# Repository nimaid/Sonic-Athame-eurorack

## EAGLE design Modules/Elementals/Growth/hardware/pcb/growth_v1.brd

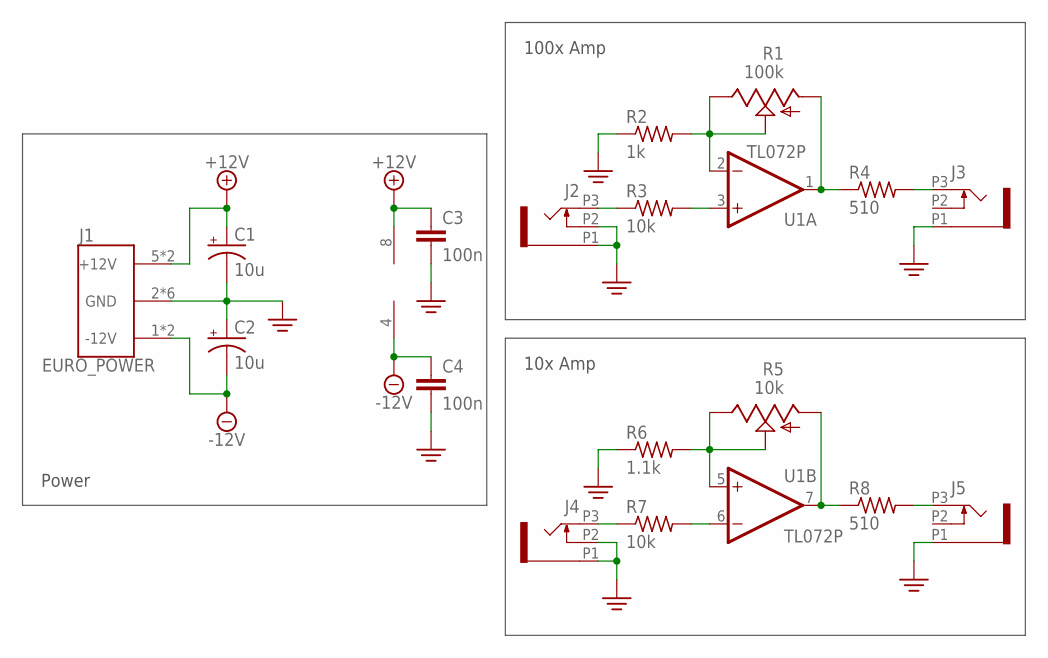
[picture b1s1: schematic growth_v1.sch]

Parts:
C1, C2: 10u; TT2D5L_FLIP
C3, C4: 100n; C025-024X044
J1: EURO_POWER
J2, J3, J4, J5: WQP-PJ398SM6; WQP_PJ_301M6
R1: 100k; ALPHA_POT_VERTICAL
R2: 1k; 0207/2V
R3, R7: 10k; 0207/2V
R4, R8: 510; 0207/2V
R5: 10k; ALPHA_POT_VERTICAL
R6: 1.1k; 0207/2V
U1: TL072P; DIL08

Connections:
+12V: C1.+, C3.1, J1.5 (+12V), J1.6 (+12V), U1.8 (V+)
-12V: C2.-, C4.1, J1.1 (-12V), J1.10 (-12V), U1.4 (V-)
GND: C1.-, C2.+, C3.2, C4.2, J1.2 (GND), J1.3 (GND), J1.4 (GND), J1.7 (GND), J1.8 (GND), J1.9 (GND), J2.P1 (1), J2.P2 (2), J3.P1 (1), J4.P1 (1), J4.P2 (2), J5.P1 (1), R2.1, R6.1
unnamed: R1.P$1 (E), R1.P$2 (S), R2.2, U1.2 (-IN)
unnamed: R1.P$3 (A), R4.1, U1.1 (OUT)
unnamed: R3.2, U1.3 (+IN)
unnamed: J2.P3 (3), R3.1
unnamed: J5.P3 (3), R8.2
unnamed: J3.P3 (3), R4.2
unnamed: R5.P$3 (A), R8.1, U1.7 (OUT)
unnamed: R5.P$1 (E), R5.P$2 (S), R6.2, U1.5 (+IN)
unnamed: R7.2, U1.6 (-IN)
unnamed: J4.P3 (3), R7.1

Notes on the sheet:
Power
100x Amp
10x Amp

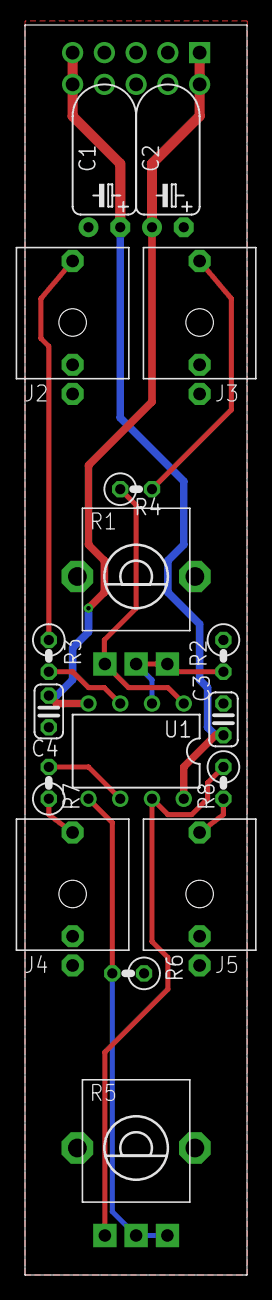
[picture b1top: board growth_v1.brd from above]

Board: 2 copper layers, 17.8 x 100.0 mm, 18 parts (1 on the bottom side), 13 nets.

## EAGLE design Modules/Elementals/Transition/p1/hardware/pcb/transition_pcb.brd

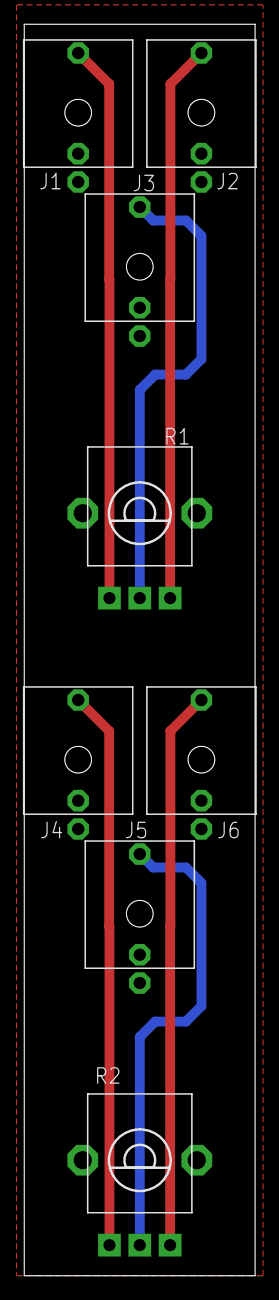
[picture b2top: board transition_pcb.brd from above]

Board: 2 copper layers, 19.0 x 103.2 mm, 10 parts (0 on the bottom side), 7 nets.

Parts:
J1, J2, J3, J4, J5, J6: WQP-PJ398SM6; WQP_PJ_301M6
R1, R2: 100k; ALPHA_POT_VERTICAL
U$1: PANEL_REF_4U
U$2: LOGO-65MIL-BSILK

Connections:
GND: J1.P1, J1.P2, J2.P1, J2.P2, J3.P1, J4.P1, J4.P2, J5.P1, J6.P1, J6.P2
unnamed: J2.P3, R1.P$1
unnamed: J3.P3, R1.P$2
unnamed: J1.P3, R1.P$3
unnamed: J4.P3, R2.P$3
unnamed: J6.P3, R2.P$1
unnamed: J5.P3, R2.P$2

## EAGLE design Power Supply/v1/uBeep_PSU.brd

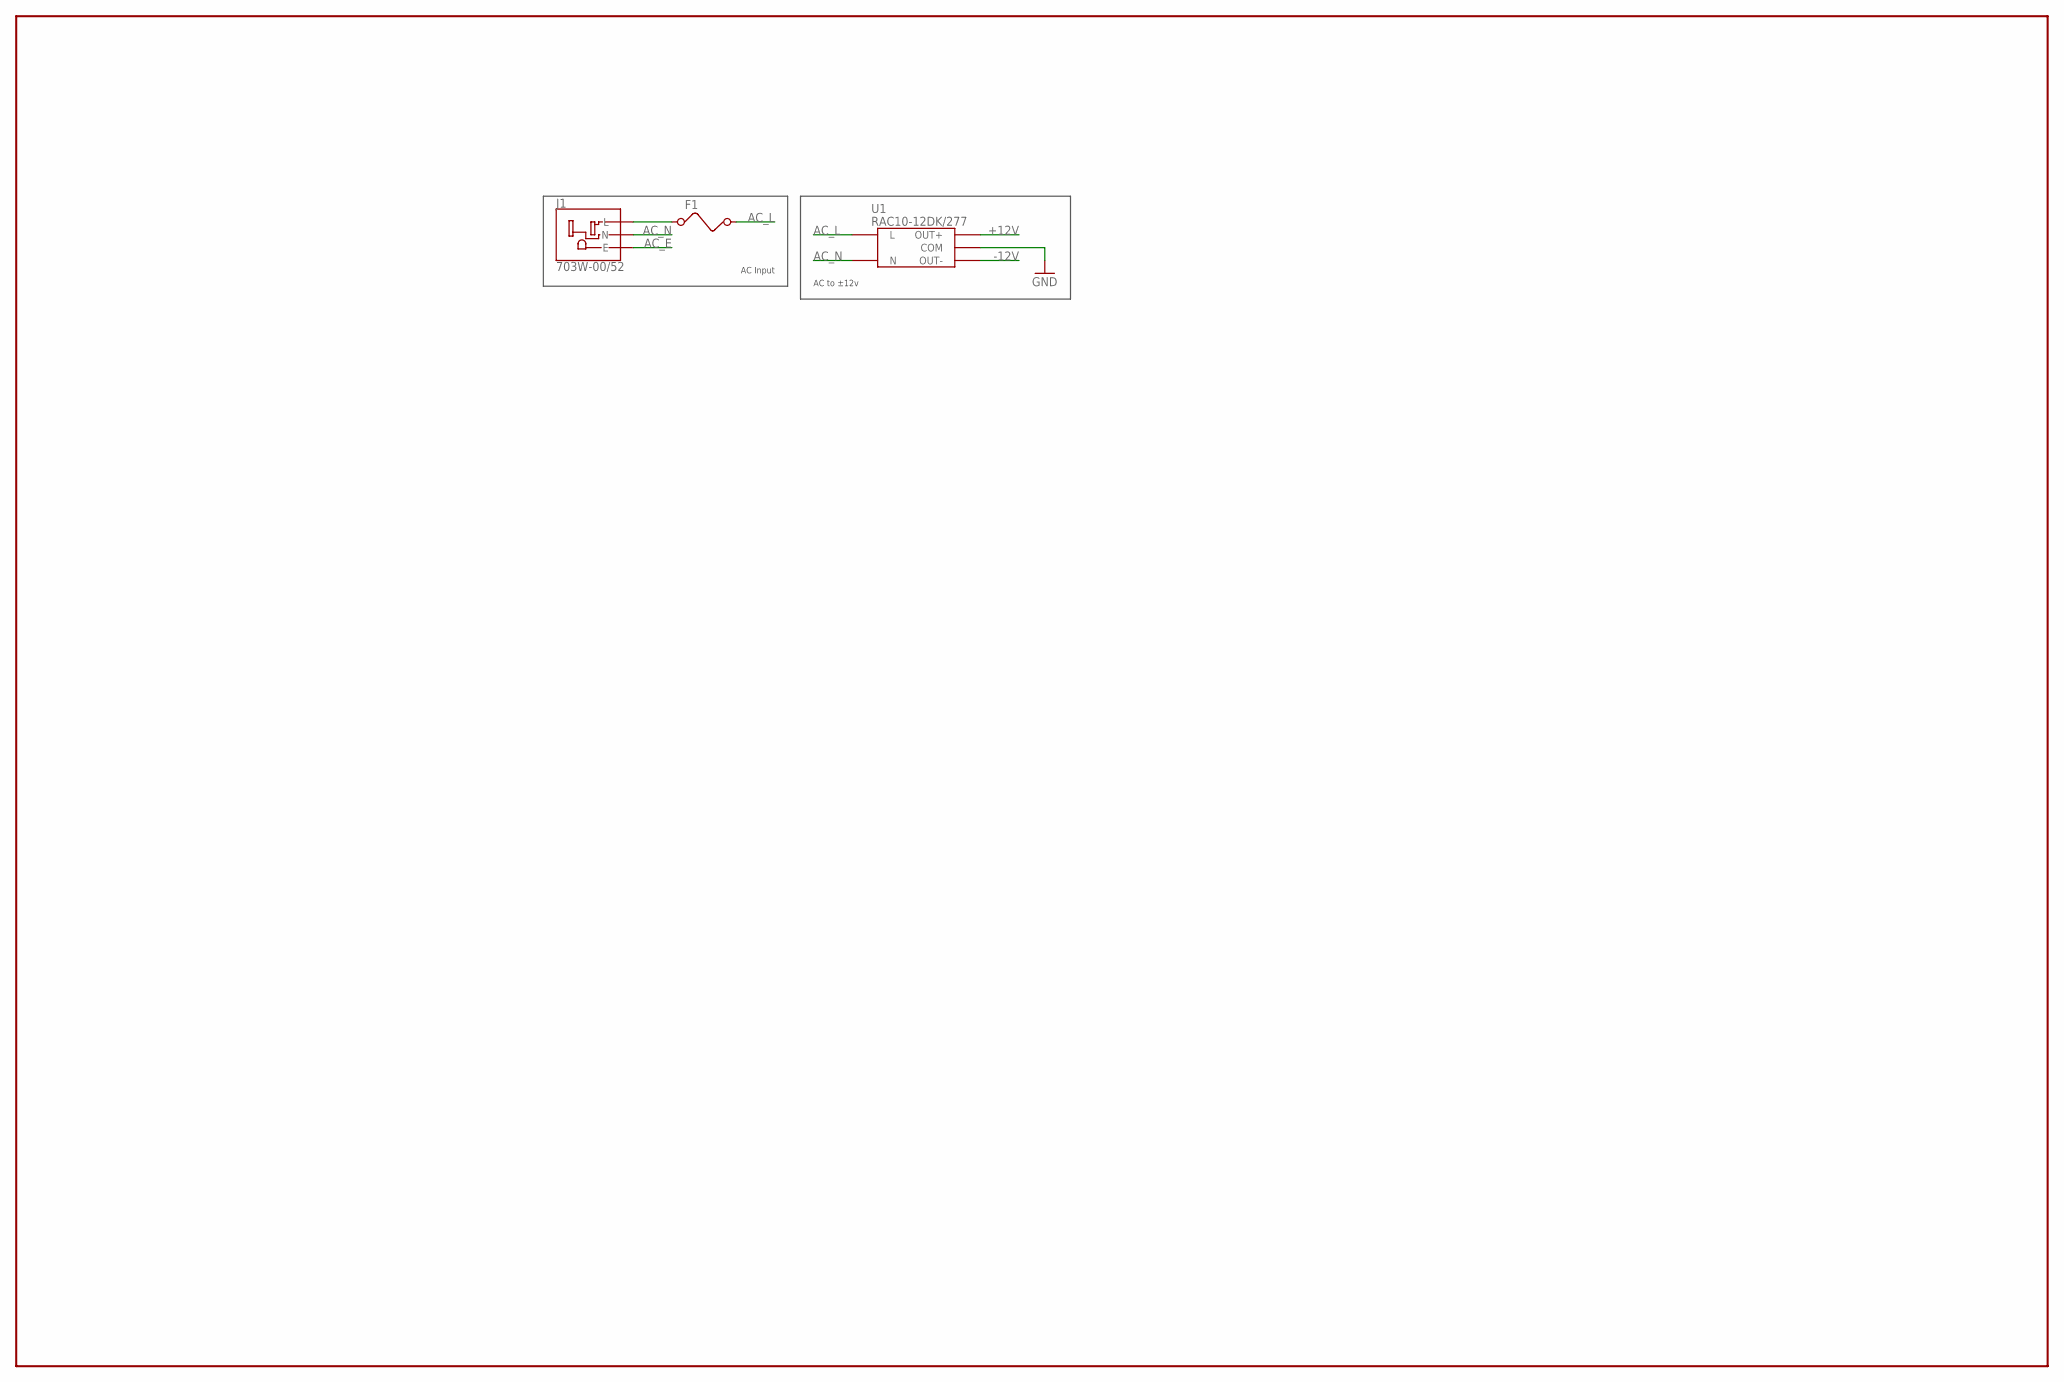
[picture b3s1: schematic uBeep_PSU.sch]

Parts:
F1: 0PTF0075P
J1: 703W-00/52
U1: RAC10-12DK/277; RAC10-DK/277

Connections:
+12V: U1.P$5 (OUT+)
-12V: U1.P$3 (OUT-)
AC_E: J1.E
AC_L: F1.2, U1.P$2 (L)
AC_N: J1.N, U1.P$1 (N)
GND: U1.P$4 (COM)
unnamed: F1.1, J1.L

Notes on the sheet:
AC to ±12v
AC Input

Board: 2 copper layers, 3 parts (0 on the bottom side), 3 nets, no tracks yet.

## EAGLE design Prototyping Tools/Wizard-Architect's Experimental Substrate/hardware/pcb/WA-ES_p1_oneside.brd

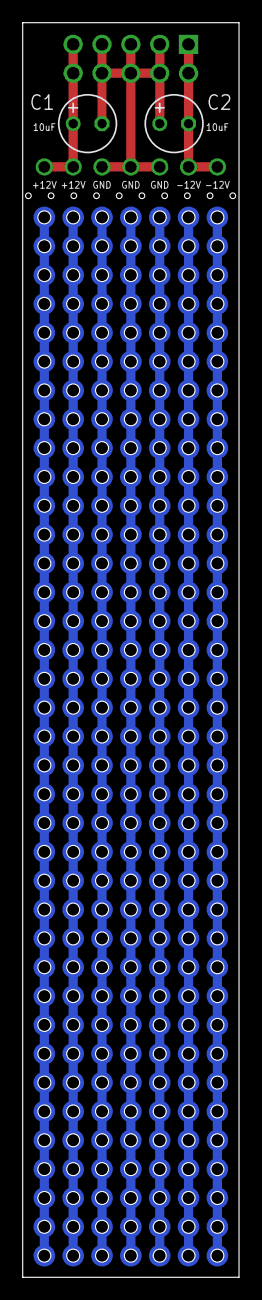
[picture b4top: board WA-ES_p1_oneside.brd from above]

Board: 2 copper layers, 19.1 x 110.5 mm, 3 parts (1 on the bottom side), 3 nets.

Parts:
C1, C2: 10u; TT2D5
J1: EURO_POWER

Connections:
+12V: C1.+, J1.5, J1.6
-12V: C2.-, J1.1, J1.10
GND: C1.-, C2.+, J1.2, J1.3, J1.4, J1.7, J1.8, J1.9

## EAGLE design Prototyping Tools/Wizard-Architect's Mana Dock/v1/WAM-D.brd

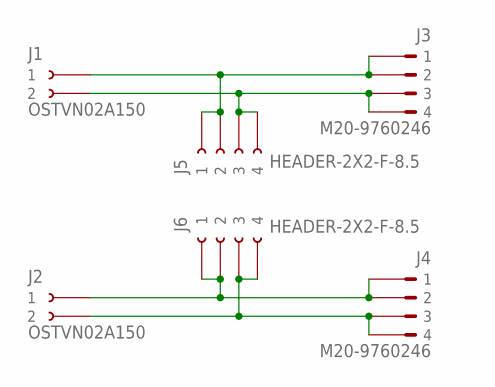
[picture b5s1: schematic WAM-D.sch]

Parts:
J1, J2: OSTVN02A150
J3, J4: M20-9760246; HDRV4W64P254_2X2_508X508X834B
J5, J6: HEADER-2X2-F-8.5; HDRVR4W75P254_2X2_558X508X850B

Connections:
unnamed: J2.P$1 (1), J4.1, J4.2, J6.1, J6.2
unnamed: J2.P$2 (2), J4.3, J4.4, J6.3, J6.4
unnamed: J1.P$2 (2), J3.3, J3.4, J5.3, J5.4
unnamed: J1.P$1 (1), J3.1, J3.2, J5.1, J5.2

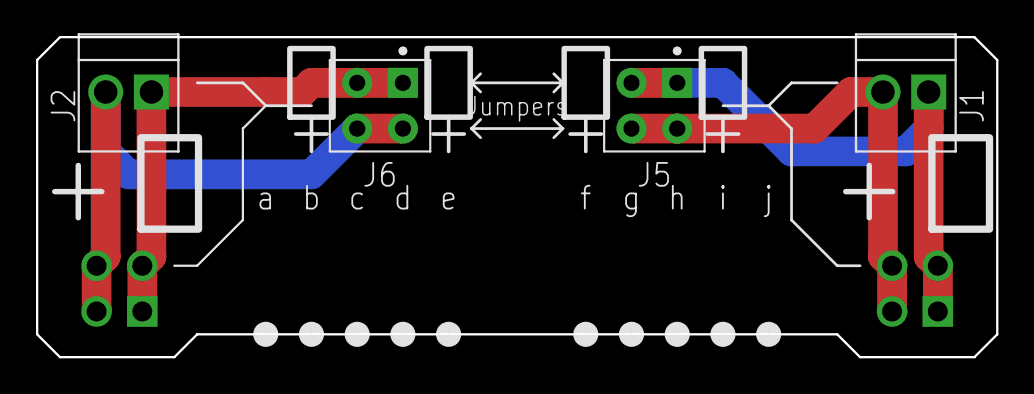
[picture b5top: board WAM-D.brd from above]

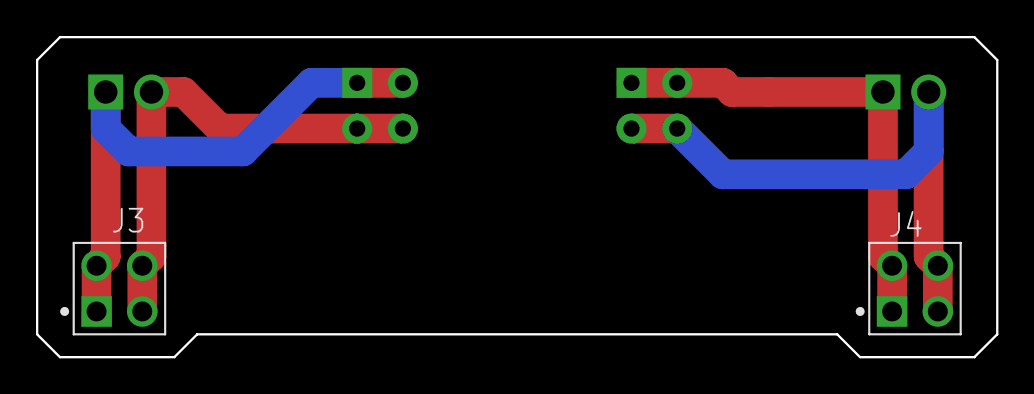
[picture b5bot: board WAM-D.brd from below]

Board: 2 copper layers, 53.3 x 17.8 mm, 6 parts (2 on the bottom side), 4 nets.
